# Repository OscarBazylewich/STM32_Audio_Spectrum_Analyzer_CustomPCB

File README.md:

# STM32 Audio Spectrum Analyzer - Custom PCB

This repository contains a small KiCad board (4 layers) for an audio spectrum analyzer. The board has an STM32L4Q5CGT6, an I2S microphone, a pin header for a Waveshare 2inch LCD Module (ST7789) and USB-C power.

This project uses an STM32L4Q5CGT6 microcontroller (MCU) to decrease the dimensions of the board. This MCU also has almost the same functions as most STM32 performance-line MCUs from ST that are applicable to this project. The initial prototype used a Nucleo-F767ZI board (refer to [Related projects](#related-projects)).

The board has these functions:

- It receives power and USB data through the USB-C receptacle.
- It reads audio from an ICS-43434 I2S microphone on the board.
- It controls the LCD module with SPI.

**Note:** This repository contains only project files (schematic Revision A, date 2026-03-31). It does not contain fabrication outputs, assembly data, test results or firmware for this board.

## Features

- STM32L4Q5CGT6: Arm Cortex-M4, a maximum of 120 MHz, 1024 KB flash, 320 KB RAM, LQFP-48 package
- USB-C for 5 V power and USB 2.0 full-speed data, with ESD protection
- SPX3819 3.3 V LDO (500 mA) that supplies one +3V3 rail for all the parts on the board
- ICS-43434 MEMS microphone (I2S, 24-bit) on the board, connected to the SAI2 pins
- 1x8 pin header for a Waveshare 2inch LCD Module (ST7789) on SPI1
- Tag-Connect TC2030 footprint for SWD
- BOOT0 and RESET switches

## Hardware

### Primary parts

| Ref | Part | Function |
| --- | --- | --- |
| U4 | STM32L4Q5CGT6 (LQFP-48) | Microcontroller |
| X1 | 16 MHz crystal (9 pF, ±10 ppm) | HSE clock |
| U1 | SPX3819M5-L-3-3 | 3.3 V, 500 mA LDO |
| J1 | USB-C receptacle, USB 2.0, 16 pins | Power and USB data |
| U2 | USBLC6-2SC6 | ESD protection on D+ / D- |
| MK1 | TDK InvenSense ICS-43434 | I2S MEMS microphone (bottom side) |
| U3 | 1x8 pin header, 2.54 mm | Connection for the Waveshare 2inch LCD Module |
| S1, S2 | Tactile switches | BOOT0 and RESET |
| J2 | Tag-Connect TC2030 footprint | SWD, SWO, NRST and +3V3 (pads and locating holes only, not in the BOM) |

The schematic contains the name of the manufacturer, the MPN and the LCSC part number of each BOM part.

### Pinout

| Interface | Signal | MCU pin | Connects to |
| --- | --- | --- | --- |
| Display | DIN | PA7 (SPI1_MOSI) | U3 pin 3 |
| Display | CLK | PA5 (SPI1_SCK) | U3 pin 4 |
| Display | CS | PA3 (GPIO) | U3 pin 5 |
| Display | DC | PA2 (GPIO) | U3 pin 6 |
| Display | RST | PA1 (GPIO) | U3 pin 7 |
| Display | BL | PA0 (GPIO) | U3 pin 8 |
| Microphone | WS | PB12 (SAI2_FS_A) | MK1 pin 1 |
| Microphone | SCK | PB13 (SAI2_SCK_A) | MK1 pin 4 |
| Microphone | SD | PB15 (SAI2_SD_A) | MK1 pin 6 |
| USB | D- | PA11 (USB_OTG_FS_DM) | J1 through U2 |
| USB | D+ | PA12 (USB_OTG_FS_DP) | J1 through U2 |
| SWD | SWDIO | PA13 | J2 pin 2 |
| SWD | RESET | NRST | J2 pin 3 |
| SWD | SWCLK | PA14 | J2 pin 4 |
| SWD | SWO | PB3 | J2 pin 6 |

The power pins are:

- U3 pin 1 and J2 pin 1 are +3V3.
- U3 pin 2 and J2 pin 5 are GND.
- On the microphone, pin 5 is VDD (+3V3) and pin 3 is GND. LR (pin 2) connects to GND.

### Board

- 94.5 x 39.7 mm, with 1 mm rounded corners and four M3 mounting holes
- 4 layers: a top layer for signals, two inner GND planes, and a bottom layer for signals and a +3V3 pour
- Approximately 1.6 mm thick, with a HAL lead-free finish, a green solder mask and a white silkscreen
- The microphone is on the bottom side. All other parts are on the top side.

## Circuit

- **Power path.** VBUS from the USB-C receptacle goes through a 2.2 µH series inductor (L1) into the SPX3819 LDO. Each side of L1 has a 2.2 µF capacitor. The LDO is on when USB power is available, because its EN pin connects to its input. One +3V3 rail supplies power to all items on the board: VDD, VDDA, VDDUSB, the Waveshare 2inch LCD Module and the microphone. VBAT also connects to +3V3, and the board has no battery for VBAT.
- **USB.** 5.1 kΩ pull-down resistors on CC1 and CC2 identify the board as a USB sink. D+ and D- go through the USBLC6-2SC6 to PA12 and PA11. The SBU pins have no connection.
- **Clock.** A 16 MHz crystal with C0G load capacitors (10 pF) connects to PH0/PH1. The crystal footprint has a front-copper keep-out area. This area prevents copper pour below the crystal. The board has no 32.768 kHz LSE crystal (PC14/PC15 have no connection).
- **Microphone.** The footprint of the ICS-43434 has a 0.5 mm hole through the board for the acoustic port of the microphone. WS, SCK and SD connect to PB12, PB13 and PB15.
- **Display.** The board has a pin header footprint for the Waveshare 2inch LCD Module. The board has a silkscreen outline with the label "2inch LCD Module". The board also has four 3.2 mm holes for the mounting holes of the LCD module. The LCD module is on the left two-thirds of the board, and all other parts are on the right third.
- **BOOT0 and RESET.** S1 connects BOOT0 (PH3) to +3V3. When S1 is open, a 10 kΩ resistor keeps BOOT0 low. S2 connects NRST to GND. Each of the two lines has a 100 nF filter capacitor.

## How to start

1. Install [KiCad](https://www.kicad.org/) 10.0 or a higher version.

   **Note:** The project files are in the KiCad 10 format. KiCad 9 and previous versions cannot open these files.

2. Clone the repository:

   ```sh
   git clone https://github.com/OscarBazylewich/STM32_Audio_Spectrum_Analyzer_CustomPCB.git
   ```

3. Open `STM32L4Q5CGT-AudioSpectrumAnalyzer.kicad_pro` in KiCad.

   **Note:** The project files contain the symbols and the footprints. Thus, KiCad opens the project without other libraries.

4. If you want the full 3D view (**View > 3D Viewer** in the PCB Editor), install the [JLCPCB KiCad Library](https://github.com/CDFER/JLCPCB-Kicad-Library) with the Plugin and Content Manager.

   **Note:** KiCad uses the `${KICAD8_3RD_PARTY}` path variable to find the 3D models for X1, S1, S2, L1 and C1.

   If KiCad does not show the 3D models of these parts, do these steps:

   1. Open **Preferences > Configure Paths**.
   2. If the list does not contain `KICAD8_3RD_PARTY`, add a path variable with this name.
   3. Set `${KICAD8_3RD_PARTY}` to the folder that contains `3dmodels/com_github_CDFER_JLCPCB-Kicad-Library`.

5. In the Schematic Editor, do the ERC.
6. In the PCB Editor, do the DRC.
7. In the PCB Editor, go to **File > Fabrication Outputs > Gerbers**.
8. Set an output folder, for example `gerbers/`.

   **Note:** The output folder in the saved plot settings is the project folder. If you do not set an output folder, KiCad writes the output files to the project folder.

9. Select the copper, mask, paste, silkscreen and Edge.Cuts layers.
10. Click **Plot**.
11. Click **Generate Drill Files...**.
12. In the **Generate Drill Files** dialog, click **Generate**.

As an alternative to steps 7 to 12, use these commands in the repository folder:

```sh
kicad-cli pcb export gerbers --output gerbers/ STM32L4Q5CGT-AudioSpectrumAnalyzer.kicad_pcb
kicad-cli pcb export drill --output gerbers/ STM32L4Q5CGT-AudioSpectrumAnalyzer.kicad_pcb
```

## Repository structure

```text
.
├── STM32L4Q5CGT-AudioSpectrumAnalyzer.kicad_pro   # KiCad 10 project: design rules, net classes, BOM fields
├── STM32L4Q5CGT-AudioSpectrumAnalyzer.kicad_sch   # Schematic on one sheet (Revision A)
├── STM32L4Q5CGT-AudioSpectrumAnalyzer.kicad_pcb   # 4-layer PCB layout, 94.5 x 39.7 mm
├── .gitattributes                                  # Lets GitHub count the KiCad files in its language statistics
├── LICENSE                                         # GNU GPL v3.0
└── README.md
```

## 3D renders

The KiCad 9.0 renders include all 3D models, but the board corners are not rounded. The KiCad 10.0 renders do not include all 3D models (the 3D models of X1, S1, S2, L1 and C1 are missing). But these renders show the added GND pour on layers 1 and 4, and the rounded corners of the board outline in this repository.

<table>
  <tr>
    <th>KiCad 9.0: top side</th>
    <th>KiCad 9.0: bottom side</th>
  </tr>
  <tr>
    <td></td>
    <td></td>
  </tr>
  <tr>
    <th>KiCad 10.0: top side</th>
    <th>KiCad 10.0: bottom side</th>
  </tr>
  <tr>
    <td></td>
    <td></td>
  </tr>
</table>

## Related projects

- [STM32_Audio_Spectrum_Analyzer_ST7789_and_INMP441](https://github.com/OscarBazylewich/STM32_Audio_Spectrum_Analyzer_ST7789_and_INMP441): This project is the initial prototype and its firmware. It uses a Nucleo-F767ZI board, an ST7789 display and an INMP441 microphone.

## Credits

- Oscar Bazylewich made this KiCad project.
- The footprints and 3D models for X1, S1, S2, L1 and C1 are from the [JLCPCB KiCad Library](https://github.com/CDFER/JLCPCB-Kicad-Library) of CDFER. The symbols for X1, S1 and S2 are also from this library.
- The symbol and the outline of the Waveshare 2inch LCD Module are from a custom library.
- All other symbols, footprints and 3D models are from the standard KiCad libraries.

## License

The license of this project is the GNU General Public License v3.0. Refer to [LICENSE](LICENSE).

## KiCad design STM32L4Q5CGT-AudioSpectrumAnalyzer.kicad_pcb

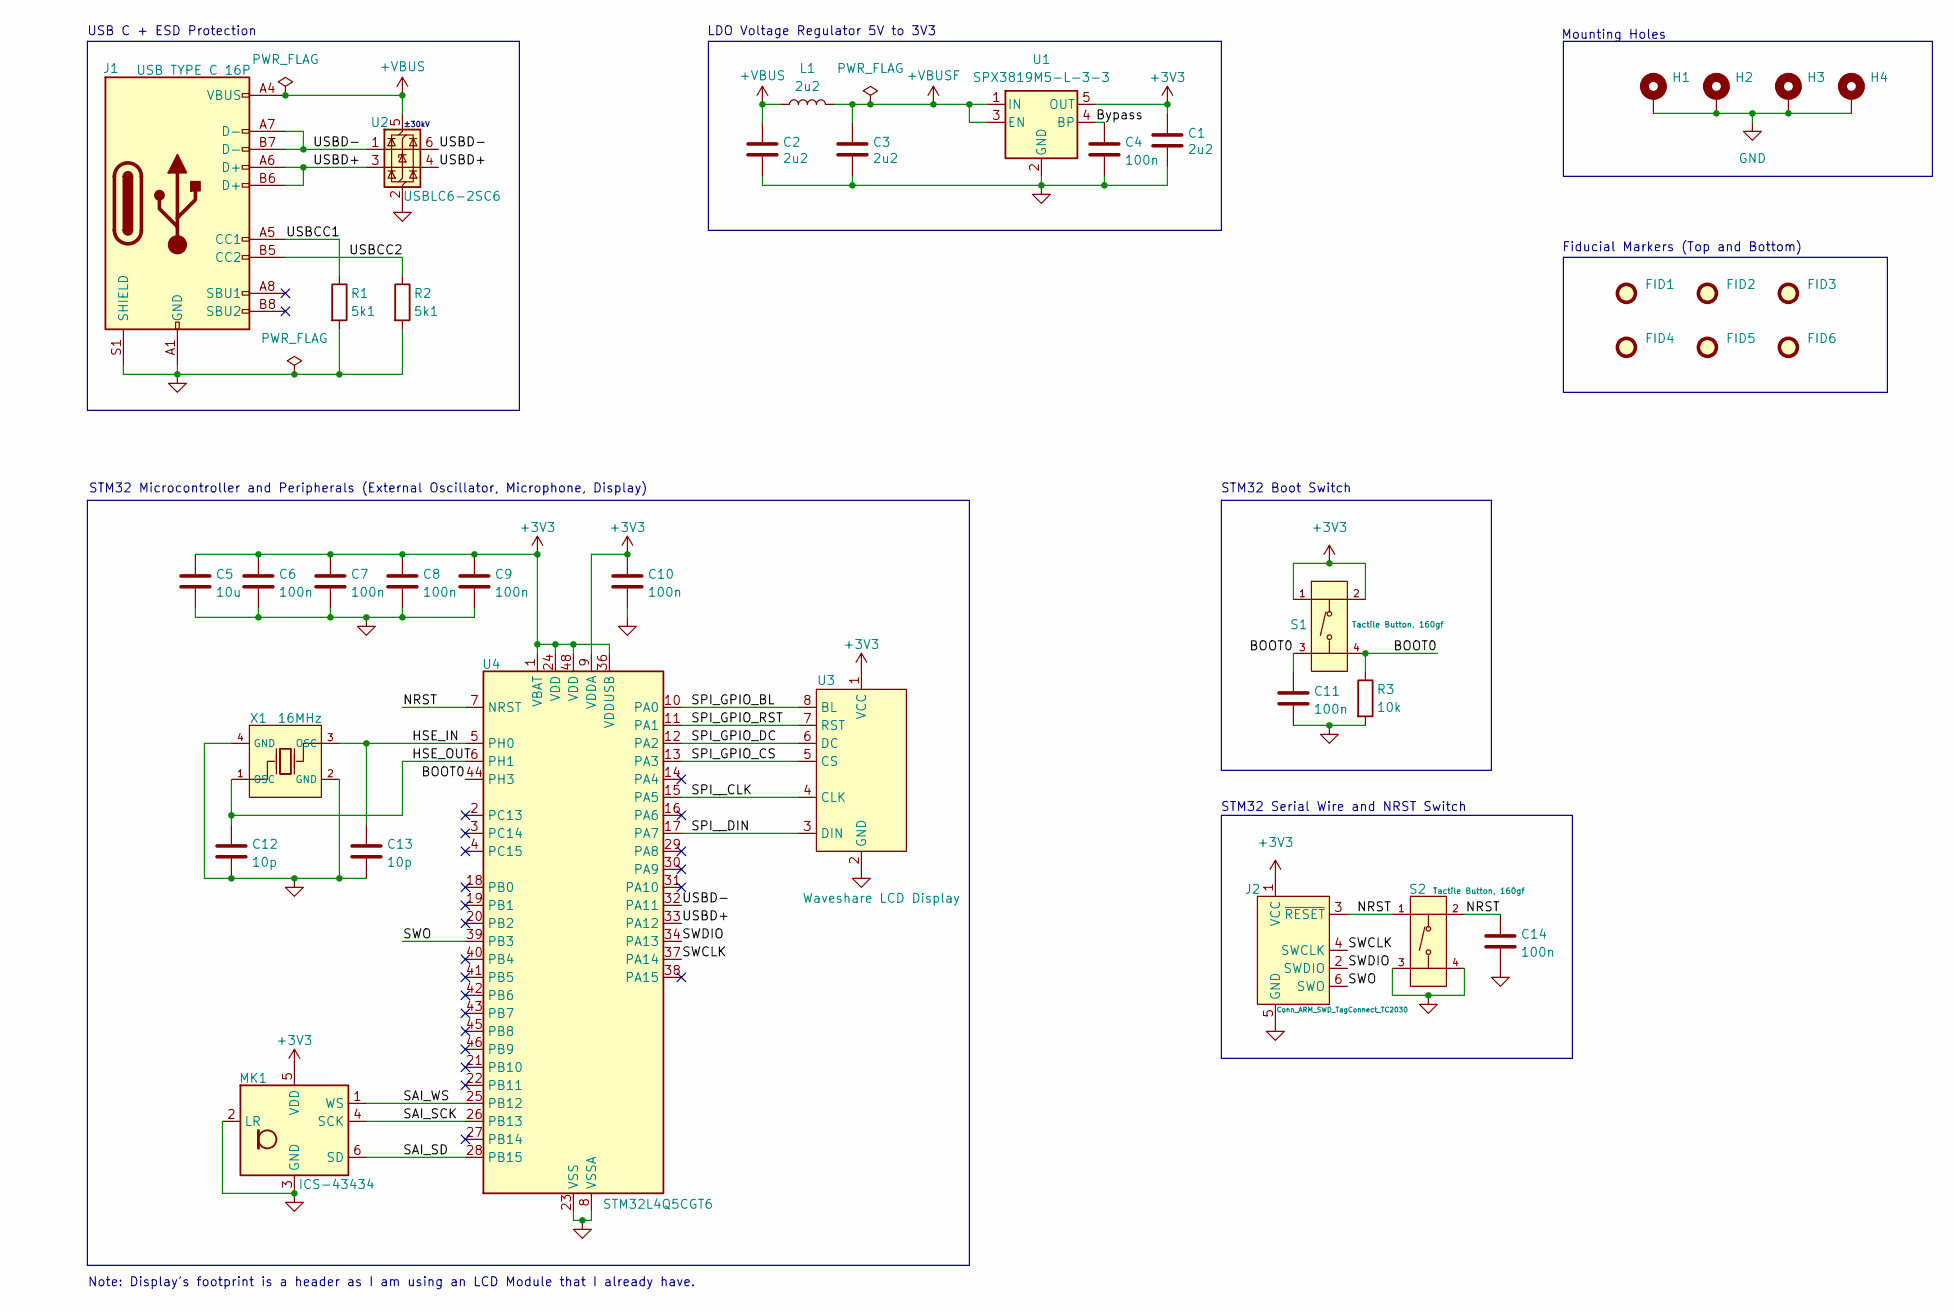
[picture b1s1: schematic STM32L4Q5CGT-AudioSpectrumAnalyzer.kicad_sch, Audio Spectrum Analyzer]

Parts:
C1: 2u2; C_CASE-A-3216-18(mm); Manufacturer Part Number T491A225K035AT; LCSC C122264
C2, C3: 2u2; C_0603_1608Metric_Pad1.08x0.95mm_HandSolder; Manufacturer Part Number CL31B225KBHNNNE; LCSC C23630
C4, C6, C7, C8, C9, C10, C11, C14: 100n; C_0402_1005Metric_Pad0.74x0.62mm_HandSolder; Manufacturer Part Number CL05B104KO5NNNC; LCSC C1525
C5: 10u; C_0603_1608Metric_Pad1.08x0.95mm_HandSolder; Manufacturer Part Number CL10A106KP8NNNC; LCSC C19702
C12, C13: 10p; C_0603_1608Metric_Pad1.08x0.95mm_HandSolder; Manufacturer Part Number CL10C100JB8NNNC; LCSC C1634
FID1, FID2, FID3, FID4, FID5, FID6: Fiducial; Fiducial_1mm_Mask2mm
H1, H2, H3, H4: MountingHole_Pad; MountingHole_3.2mm_M3_Pad
J1: USB TYPE C 16P; USB_C_Receptacle_GCT_USB4105-xx-A_16P_TopMnt_Horizontal; Manufacturer Part Number KH-TYPE-C-16P; LCSC C709357
J2: Conn_ARM_SWD_TagConnect_TC2030; Tag-Connect_TC2030-IDC-FP_2x03_P1.27mm_Vertical
L1: 2u2; L_1206; Manufacturer Part Number LQM31PN2R2M00L; LCSC C171763
MK1: ICS-43434; InvenSense_ICS-43434-6_3.5x2.65mm; Manufacturer Part Number ICS-43434; LCSC C5656610
R1, R2: 5k1; R_0402_1005Metric_Pad0.72x0.64mm_HandSolder; Manufacturer Part Number 0402WGF5101TCE; LCSC C25905
R3: 10k; R_0402_1005Metric_Pad0.72x0.64mm_HandSolder; Manufacturer Part Number 0402WGF1002TCE; LCSC C25744
S1, S2: Tactile Button, 160gf; SW-SMD_4P-L5.1-W5.1-P3.70-LS6.5-TL-2; Manufacturer Part Number TS-1187A-B-A-B; LCSC C318884
U1: SPX3819M5-L-3-3; SOT-23-5; Manufacturer Part Number SPX3819M5-L-3-3/TR; LCSC C9055
U2: USBLC6-2SC6; SOT-23-6; Manufacturer Part Number USBLC6-2SC6; LCSC C2687116
U3: Waveshare LCD Display; PinHeader_1x08_P2.54mm_Vertical; Manufacturer Part Number 2.54-1*8; LCSC C5156616
U4: STM32L4Q5CGT6; LQFP-48_7x7mm_P0.5mm; Manufacturer Part Number STM32L4Q5CGT6; LCSC C1236662
X1: 16MHz; OSC-SMD_4P-L3.2-W2.5-BL; Manufacturer Part Number X322516MLB4SI; LCSC C13738

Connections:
+3V3: C1.1, C5.1, C6.1, C7.1, C8.1, C9.1, C10.1, J2.1 (VCC), MK1.5 (VDD), S1.1 (A), S1.2 (B), U1.5 (OUT), U3.1 (VCC), U4.1 (VBAT), U4.9 (VDDA), U4.24 (VDD), U4.36 (VDDUSB), U4.48 (VDD)
+VBUS: C2.1, J1.A4 (VBUS), J1.A9 (VBUS), J1.B4 (VBUS), J1.B9 (VBUS), L1.1, U2.5 (VBUS)
+VBUSF: C3.1, L1.2, U1.1 (IN), U1.3 (EN)
/BOOT0: C11.1, R3.1, S1.3 (C), S1.4 (D), U4.44 (PH3)
/Bypass: C4.1, U1.4 (BP)
/HSE_IN: C13.1, U4.5 (PH0), X1.3 (OSC)
/HSE_OUT: C12.1, U4.6 (PH1), X1.1 (OSC)
/NRST: C14.1, J2.3 (~RESET), S2.1 (A), S2.2 (B), U4.7 (NRST)
/SAI_SCK: MK1.4 (SCK), U4.26 (PB13)
/SAI_SD: MK1.6 (SD), U4.28 (PB15)
/SAI_WS: MK1.1 (WS), U4.25 (PB12)
/SPI_GPIO_BL: U3.8 (BL), U4.10 (PA0)
/SPI_GPIO_CS: U3.5 (CS), U4.13 (PA3)
/SPI_GPIO_DC: U3.6 (DC), U4.12 (PA2)
/SPI_GPIO_RST: U3.7 (RST), U4.11 (PA1)
/SPI__CLK: U3.4 (CLK), U4.15 (PA5)
/SPI__DIN: U3.3 (DIN), U4.17 (PA7)
/SWCLK: J2.4 (SWCLK), U4.37 (PA14)
/SWDIO: J2.2 (SWDIO), U4.34 (PA13)
/SWO: J2.6 (SWO), U4.39 (PB3)
/USBCC1: J1.A5 (CC1), R1.1
/USBCC2: J1.B5 (CC2), R2.1
/USBD+: J1.A6 (D+), J1.B6 (D+), U2.3 (I/O2), U2.4 (I/O2), U4.33 (PA12)
/USBD-: J1.A7 (D-), J1.B7 (D-), U2.1 (I/O1), U2.6 (I/O1), U4.32 (PA11)
GND: C1.2, C2.2, C3.2, C4.2, C5.2, C6.2, C7.2, C8.2, C9.2, C10.2, C11.2, C12.2, C13.2, C14.2, H1.1 (1_1), H2.1 (1_1), H3.1 (1_1), H4.1 (1_1), J1.A1 (GND), J1.A12 (GND), J1.B1 (GND), J1.B12 (GND), J1.S1 (SHIELD), J2.5 (GND), MK1.2 (LR), MK1.3 (GND), R1.2, R2.2, R3.2, S2.3 (C), S2.4 (D), U1.2 (GND), U2.2 (GND), U3.2 (GND), U4.8 (VSSA), U4.23 (VSS), U4.35 (VSS), U4.47 (VSS), X1.2 (GND), X1.4 (GND)

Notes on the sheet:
LDO Voltage Regulator 5V to 3V3
STM32 Boot Switch
STM32 Microcontroller and Peripherals (External Oscillator, Microphone, Display)
STM32 Serial Wire and NRST Switch
Mounting Holes
±30kV
Note: Display's footprint is a header as I am using an LCD Module that I already have.
Fiducial Markers (Top and Bottom)
USB C + ESD Protection

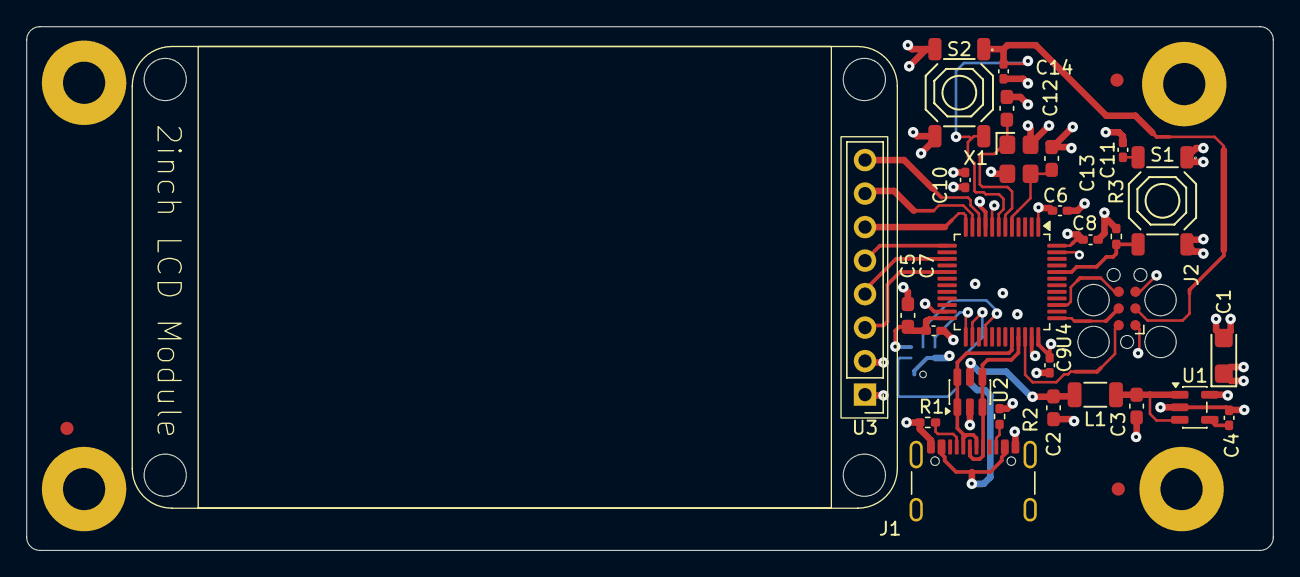
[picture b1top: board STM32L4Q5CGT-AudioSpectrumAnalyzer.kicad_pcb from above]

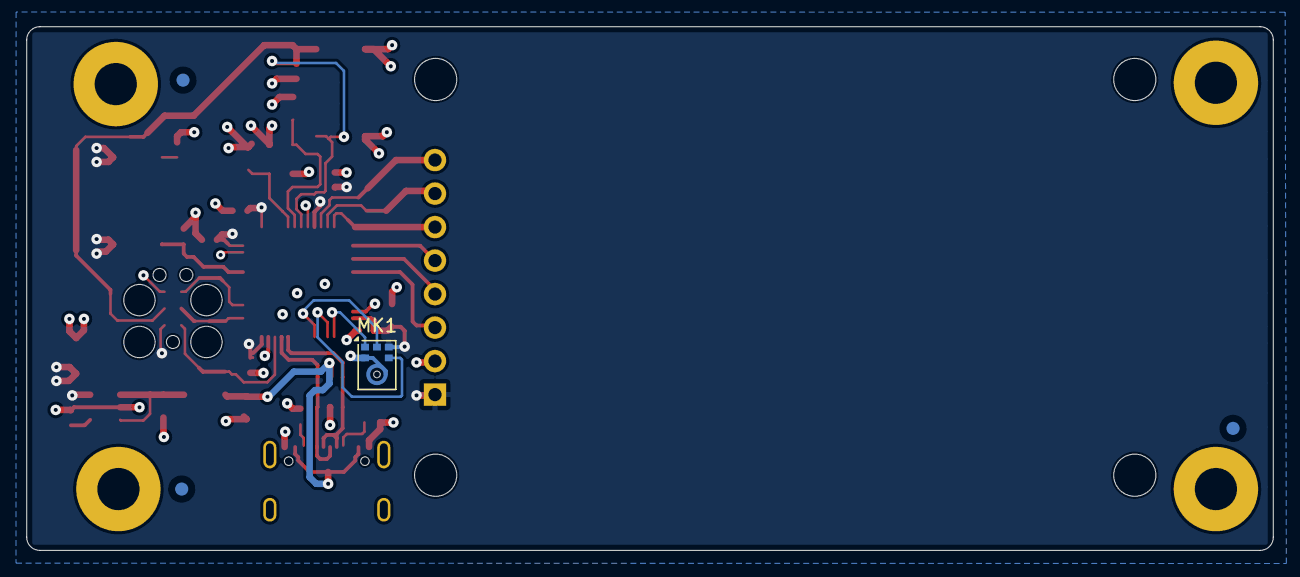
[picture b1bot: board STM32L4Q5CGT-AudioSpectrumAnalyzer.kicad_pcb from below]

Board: 4 copper layers, 94.5 x 39.7 mm, 38 parts (4 on the bottom side), 25 nets.

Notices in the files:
README.md:
License: GPL-3.0
